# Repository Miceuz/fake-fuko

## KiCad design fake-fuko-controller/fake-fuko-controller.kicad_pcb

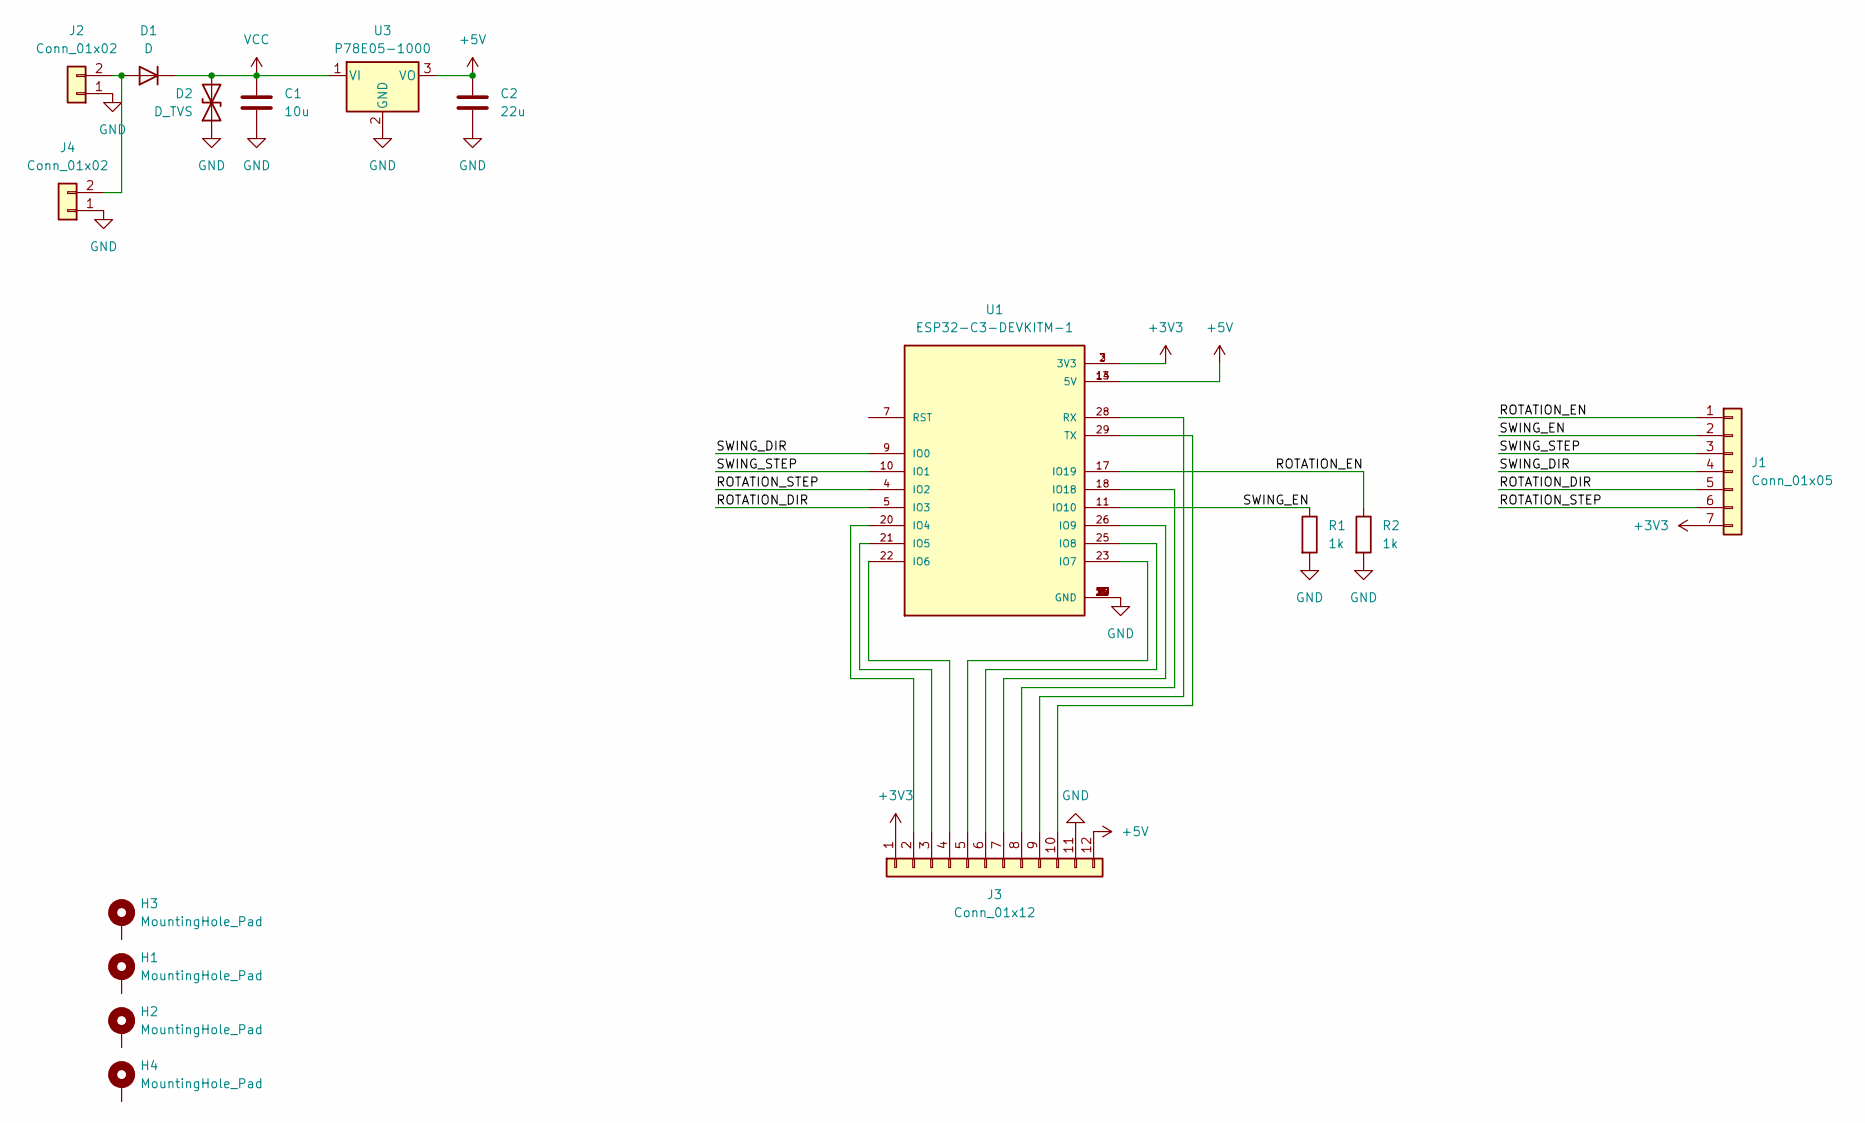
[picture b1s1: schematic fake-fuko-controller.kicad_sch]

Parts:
C1: 10u; C_2220_5650Metric; PartNo C5750X7R1H106K230KB
C2: 22u; C_2220_5650Metric; PartNo C5750X7R1E226M250KA
D1: D; D_SMA
D2: D_TVS; D_SMA
H1, H2, H3, H4: MountingHole_Pad; MountingHole_3.2mm_M3_DIN965_Pad
J1: Conn_01x05; MOLEX_2157601007; PartNo 2157601007
J2, J4: Conn_01x02; MOLEX_2157601002; PartNo 2157601002
J3: Conn_01x12; PinHeader_1x12_P2.54mm_Vertical
R1, R2: 1k; R_0603_1608Metric
U1: ESP32-C3-DEVKITM-1; XCVR_ESP32-C3-DEVKITM-1; PartNo ESP32-C3-DEVKITM-1
U3: P78E05-1000; CONV_P78E05-1000; PartNo P78E05-1000

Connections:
+3V3: J1.7, J3.1, U1.2 (3V3), U1.3 (3V3)
+5V: C2.1, J3.12, U1.13 (5V), U1.14 (5V), U3.3 (VO)
/ROTATION_DIR: J1.5, U1.5 (IO3)
/ROTATION_EN: J1.1, R2.1, U1.17 (IO19)
/ROTATION_STEP: J1.6, U1.4 (IO2)
/SWING_DIR: J1.4, U1.9 (IO0)
/SWING_EN: J1.2, R1.1, U1.11 (IO10)
/SWING_STEP: J1.3, U1.10 (IO1)
GND: C1.2, C2.2, D2.1 (A1), J2.1, J3.11, J4.1, R1.2, R2.2, U1.1 (GND), U1.6 (GND), U1.8 (GND), U1.12 (GND), U1.15 (GND), U1.16 (GND), U1.19 (GND), U1.24 (GND), U1.27 (GND), U1.30 (GND), U3.2 (GND)
unnamed: D1.2 (A), J2.2, J4.2
unnamed: J3.2, U1.20 (IO4)
unnamed: J3.3, U1.21 (IO5)
unnamed: J3.4, U1.22 (IO6)
unnamed: J3.5, U1.23 (IO7)
unnamed: J3.6, U1.25 (IO8)
unnamed: J3.7, U1.26 (IO9)
unnamed: J3.8, U1.18 (IO18)
unnamed: J3.9, U1.28 (RX)
unnamed: J3.10, U1.29 (TX)
VCC: C1.1, D1.1 (K), D2.2 (A2), U3.1 (VI)

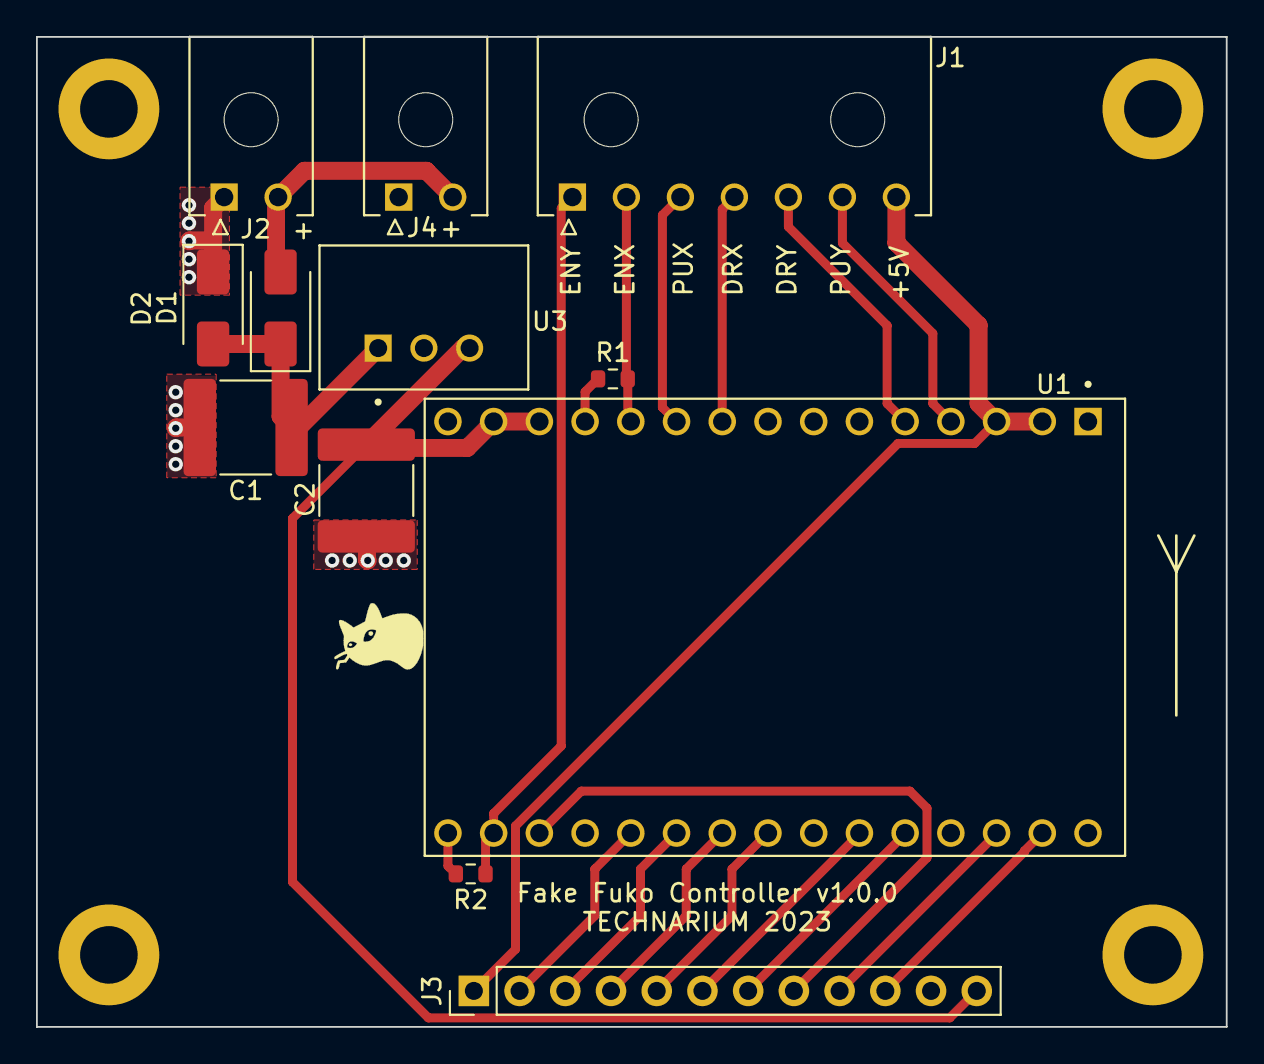
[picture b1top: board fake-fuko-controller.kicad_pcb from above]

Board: 2 copper layers, 66.1 x 55.0 mm, 16 parts (0 on the bottom side), 20 nets.

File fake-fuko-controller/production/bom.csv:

Designator,Footprint,Quantity,Value,LCSC Part #
C1,C_2220_5650Metric,1,10u,
C2,C_2220_5650Metric,1,22u,
D1,D_SMA,1,D,
D2,D_SMA,1,D_TVS,
"H1, H2, H3, H4",MountingHole_3.2mm_M3_DIN965_Pad,4,MountingHole_Pad,
J1,MOLEX_2157601007,1,Conn_01x05,
"J2, J4",MOLEX_2157601002,2,Conn_01x02,
J3,PinHeader_1x12_P2.54mm_Vertical,1,Conn_01x12,
"R1, R2",R_0603_1608Metric,2,1k,
U1,XCVR_ESP32-C3-DEVKITM-1,1,ESP32-C3-DEVKITM-1,
U3,CONV_P78E05-1000,1,P78E05-1000,

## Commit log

2023-09-06 Add kicad board and firmware files
2023-09-07 Add bom
2023-09-07 Add diode partnos
